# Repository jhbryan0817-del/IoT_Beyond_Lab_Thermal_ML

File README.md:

# Edge Thermal Occupancy ML @ HKU

We introduce the privacy-oriented occupancy inference system using a telemetry of distributed 32 × 24 thermal nodes, which is used to train a model that accurately infers the availability of a specific area with unique context. Libraries at HKU, such as the Chi Wah Learning Commons, are unique in that there are no strictly defined seats. Availability is highly subjective due to many variables present. Therefore, the thermal matrix will be paired directly against the perceived availability score, which would be considered the ground truth. The goal is to create a system that is mature enough to provide useful qualitative information to students who are making decisions throughout their day.

## Target System Architecture

- Each node captures low-resolution thermal frames within a defined zone.
- The edge model maps thermal data directly to an availability estimate.
- The node transmits a packet consisting of the zone identifier, normalized availability estimate, confidence value, timestamp, and system metadata.
- LoRa provides node-to-server communication.
- The server consolidates zone-level estimates for downstream display interfaces and services.

## Repository Structure

- `Thermal_CAD/` — Rev B Fusion enclosure with a flat front, protruding thermal sensor, rear access for a 50 × 40 × 8 mm 2000 mAh battery, locating lid collars, and independent direct-thread M3 mounts. Includes three printable STL parts, STEP exports, previews and CAD/mesh checks. See [assembly notes](Thermal_CAD/Design-and-assembly-notes.md).

- `Hardware/` — HKU Thermal Node Rev 1.1 carrier: MLX90640 thermal sensor positioned away from module heat, corrected local power conditioning, an 80 × 40 mm enclosure-friendly outline, and I²C mapped to Heltec V3 GPIO41/GPIO42 instead of reserved pins. Includes KiCad sources, project-local libraries, BOMs, and the retained hardware licence.

## Lineage and Acknowledgements

Hardware Rev 1.1 is derived from the GPL-3.0 [CrowdAware node](https://github.com/crowdaware-inno-wing-iot/crowdaware-node). It keeps the original low-resolution thermal-node concept while improving thermal separation, decoupling, mechanics, source portability, and Heltec V3 pin compatibility. Attribution and a copy of the applicable licence are retained in `Hardware/`.

## About IoT Beyond Lab

Established in September 2026, the team is based in Innovation Wing at the University of Hong Kong. The mission is to build and **deploy** different IoT applications that will leave a lasting impact, hence inspiring the name "IoT Beyond Lab". Other than this thermal ML project, the team also partners with Chulalongkorn University (CSII) in Thailand to develop IoT-based solutions that mitigates flood-induced disaster impact.

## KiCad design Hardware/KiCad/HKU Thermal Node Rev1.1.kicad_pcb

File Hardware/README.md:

# HKU Thermal Node Rev 1.1

Rev 1.1 is the current carrier-board design for a Heltec WiFi LoRa 32 V3 and MLX90640 low-resolution thermal occupancy node.

## Hardware definition

| Property | Specification |
|---|---|
| Board | 80 × 40 mm, two copper layers, four M3 mounting holes |
| Sensor | MLX90640ESF-BAA-000-TU, 32 × 24 pixels, 110° × 75° field of view |
| Controller/radio | Heltec WiFi LoRa 32 V3 with frequency-matched external antenna |
| Module connection | Two 1×18, 2.54 mm female socket strips |
| SDA | GPIO41, Heltec J3 pin 15, carrier J1 pad 7 |
| SCL | GPIO42, Heltec J3 pin 16, carrier J1 pad 5 |
| Sensor supply | Switchable 3.3 V `V_EXT`; GPIO36 active-low enable |
| Pull-ups | `R1`, `R2`: 1 kΩ to `V_EXT` |
| Decoupling | `C1`: 100 nF; `C2`: 10 µF |
| Factory-SMT scope | `C1`, `C2`, `R1`, `R2` |
| Manual scope | `A1`, two socket strips represented by `J1`, Heltec module, antenna, and mechanics |

## Rev 1.1 changes from CrowdAware

| Change | Reason |
|---|---|
| MLX90640 moved outside the Heltec footprint | Reduces heating influence from the controller, display, regulator, and radio while giving the sensor a clearer field region. |
| Board changed to an 80 × 40 mm rectangle with four M3 holes | Defines a regular mechanical and enclosure interface. |
| Sensor decoupling changed to 100 nF local plus 10 µF bulk capacitance | Improves the local sensor supply arrangement. |
| I²C pull-ups connected to `V_EXT` instead of always-on `3V3` | Keeps the bus high level in the sensor power domain and avoids back-powering when that rail is disabled. |
| SDA moved to GPIO41/J1 pad 7 and SCL moved to GPIO42/J1 pad 5 | Avoids reserved Heltec V3 GPIO34/GPIO33 and matches the intended firmware mapping. |
| `V_EXT` connection changed from a local copper island to an explicit trace | Makes the switched power path unambiguous. |
| Module sockets corrected from 1×20 to 1×18 | Matches the Heltec WiFi LoRa 32 V3 pin count and footprint. |
| MLX90640 and passive order codes corrected | Aligns the design with the specified sensor package and active component selections. |
| Project-local symbols and footprints added | Keeps the Rev 1.1 KiCad source portable and internally consistent. |
| Silkscreen identifies `Thermal Node Occupancy ML`, Rev 1.1, HKU Innovation Wing IoT Beyond Lab, and its CrowdAware basis | Tailors the carrier to the HKU deployment while preserving upstream credit on the board. |

Rev 1.1 is derived from the GPL-3.0 CrowdAware node. The full acknowledgement is in the repository-level `README.md`, and the retained licence is `COPYING-HARDWARE-GPL-3.0.txt`.

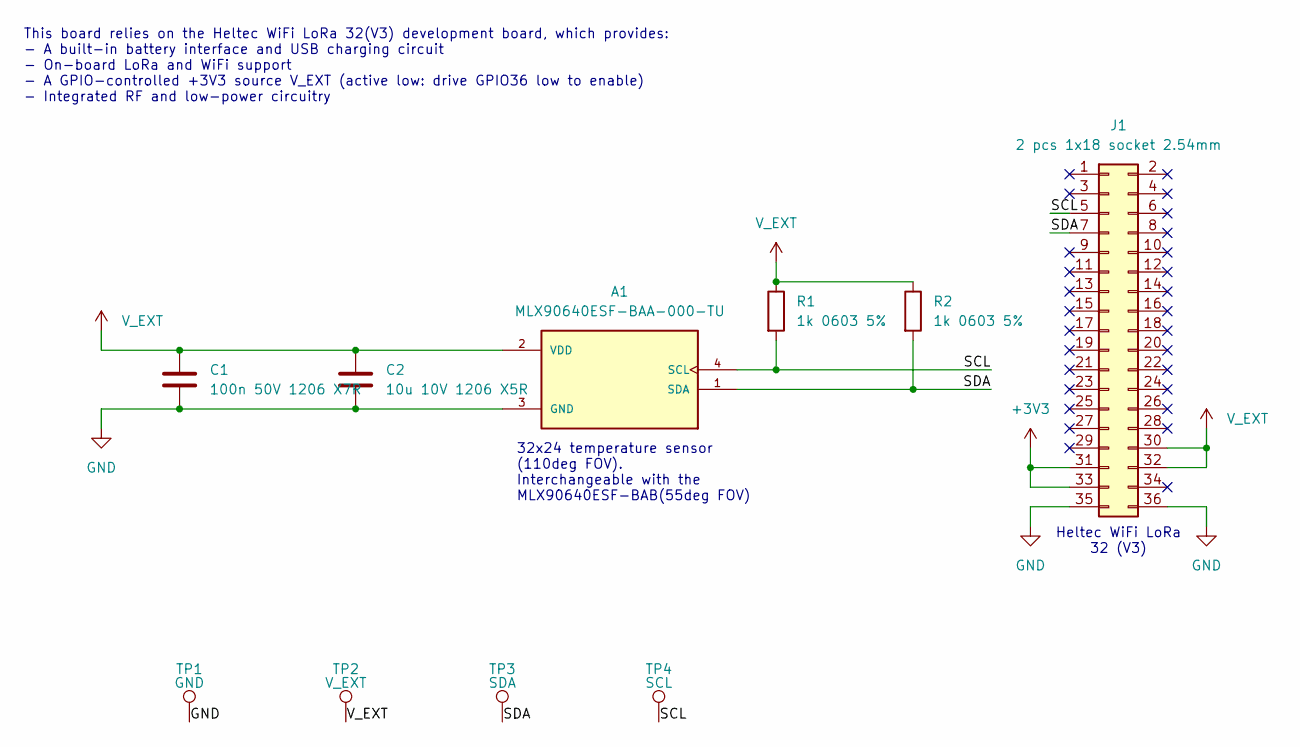
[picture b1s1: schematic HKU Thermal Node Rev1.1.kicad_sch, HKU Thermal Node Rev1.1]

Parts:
A1: MLX90640ESF-BAA-000-TU; PARTREV 11; Mouser No. 482-MLX90640ESFBAATU
C1: 100n 50V 1206 X7R; C_1206_3216Metric_Pad1.33x1.80mm_HandSolder; Mouser No. 80-C1206C104K5RAC
C2: 10u 10V 1206 X5R; C_1206_3216Metric_Pad1.33x1.80mm_HandSolder; Mouser No. 80-C1206C106K8P
J1: 2 pcs 1x18 socket 2.54mm; Connector_HeltecWiFiLoRa32v3; Mouser No. 200-SSW11801GS (order 2)
R1, R2: 1k 0603 5%; R_0603_1608Metric_Pad0.98x0.95mm_HandSolder; Mouser No. 603-SR0603JR-7T1KL
TP1: GND; TestPoint_Plated_Hole_D2.0mm
TP2: V_EXT; TestPoint_Plated_Hole_D2.0mm
TP3: SDA; TestPoint_Plated_Hole_D2.0mm
TP4: SCL; TestPoint_Plated_Hole_D2.0mm

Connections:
+3V3: J1.31, J1.33
/SCL: A1.4 (SCL), J1.5, R1.2, TP4.1
/SDA: A1.1 (SDA), J1.7, R2.2, TP3.1
GND: A1.3 (GND), C1.2, C2.2, J1.35, J1.36, TP1.1
V_EXT: A1.2 (VDD), C1.1, C2.1, J1.30, J1.32, R1.1, R2.1, TP2.1

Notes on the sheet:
This board relies on the Heltec WiFi LoRa 32(V3) development board, which provides: - A built-in battery interface and USB charging circuit - On-board LoRa and WiFi support - A GPIO-controlled +3V3 source V_EXT (active low: drive GPIO36 low to enable) - Integrated RF and low-power circuitry
Heltec WiFi LoRa 32 (V3)
32x24 temperature sensor (110deg FOV). Interchangeable with the MLX90640ESF-BAB(55deg FOV)

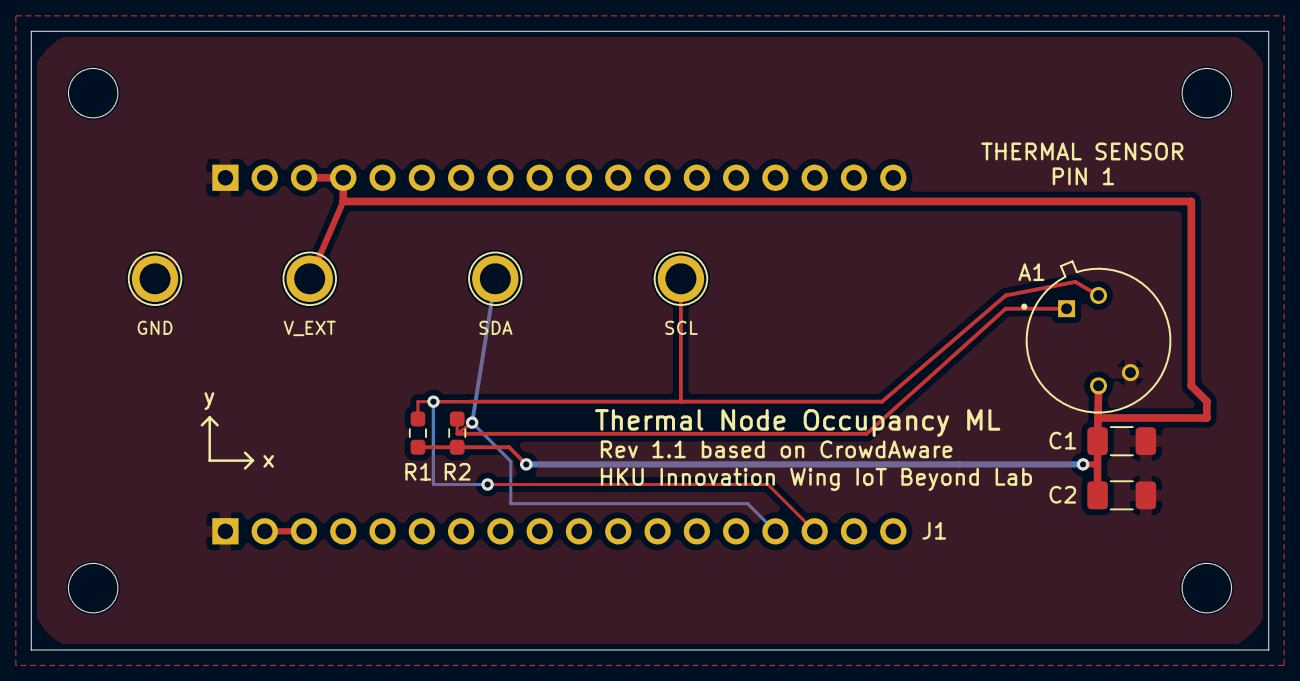
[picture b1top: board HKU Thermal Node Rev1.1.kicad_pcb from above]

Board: 2 copper layers, 80.0 x 40.0 mm, 14 parts (1 on the bottom side), 5 nets.

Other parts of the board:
H1, H2, H3, H4: MountingHole_3.2mm_M3

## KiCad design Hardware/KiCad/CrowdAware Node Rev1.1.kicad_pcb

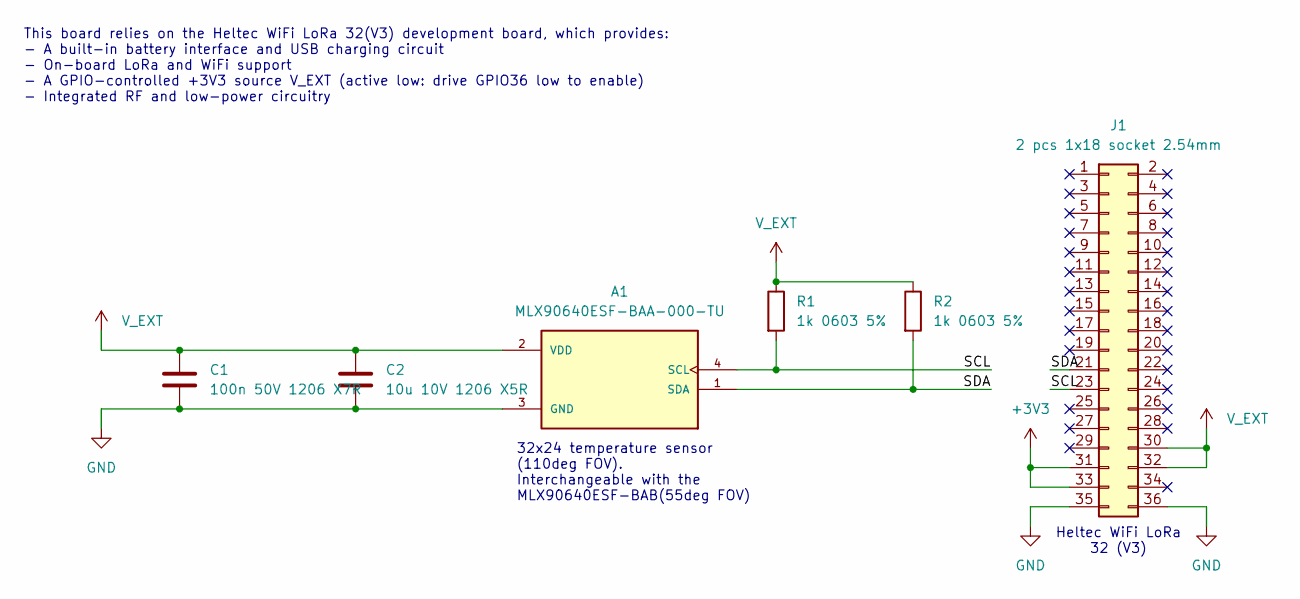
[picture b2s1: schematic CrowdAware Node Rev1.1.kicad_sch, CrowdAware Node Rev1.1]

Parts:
A1: MLX90640ESF-BAA-000-TU; PARTREV 11; Mouser No. 482-MLX90640ESFBAATU
C1: 100n 50V 1206 X7R; C_1206_3216Metric_Pad1.33x1.80mm_HandSolder; Mouser No. 80-C1206C104K5RAC
C2: 10u 10V 1206 X5R; C_1206_3216Metric_Pad1.33x1.80mm_HandSolder; Mouser No. 80-C1206C106K8P
J1: 2 pcs 1x18 socket 2.54mm; Connector_HeltecWiFiLoRa32v3; Mouser No. 200-SSW11801GS (order 2)
R1, R2: 1k 0603 5%; R_0603_1608Metric_Pad0.98x0.95mm_HandSolder; Mouser No. 603-SR0603JR-7T1KL

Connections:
+3V3: J1.31, J1.33
/SCL: A1.4 (SCL), J1.23, R1.2
/SDA: A1.1 (SDA), J1.21, R2.2
GND: A1.3 (GND), C1.2, C2.2, J1.35, J1.36
V_EXT: A1.2 (VDD), C1.1, C2.1, J1.30, J1.32, R1.1, R2.1

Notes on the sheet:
This board relies on the Heltec WiFi LoRa 32(V3) development board, which provides: - A built-in battery interface and USB charging circuit - On-board LoRa and WiFi support - A GPIO-controlled +3V3 source V_EXT (active low: drive GPIO36 low to enable) - Integrated RF and low-power circuitry
Heltec WiFi LoRa 32 (V3)
32x24 temperature sensor (110deg FOV). Interchangeable with the MLX90640ESF-BAB(55deg FOV)

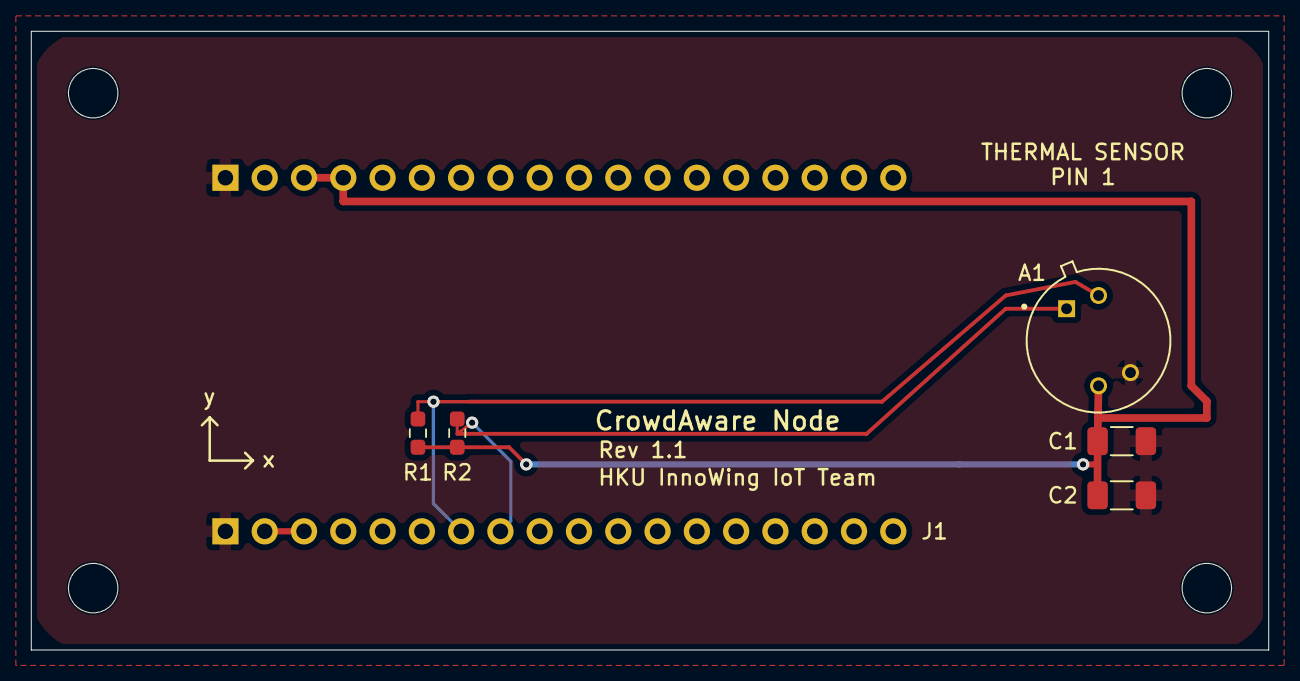
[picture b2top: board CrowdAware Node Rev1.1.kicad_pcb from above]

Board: 2 copper layers, 80.0 x 40.0 mm, 10 parts (1 on the bottom side), 5 nets.

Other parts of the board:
H1, H2, H3, H4: MountingHole_3.2mm_M3
